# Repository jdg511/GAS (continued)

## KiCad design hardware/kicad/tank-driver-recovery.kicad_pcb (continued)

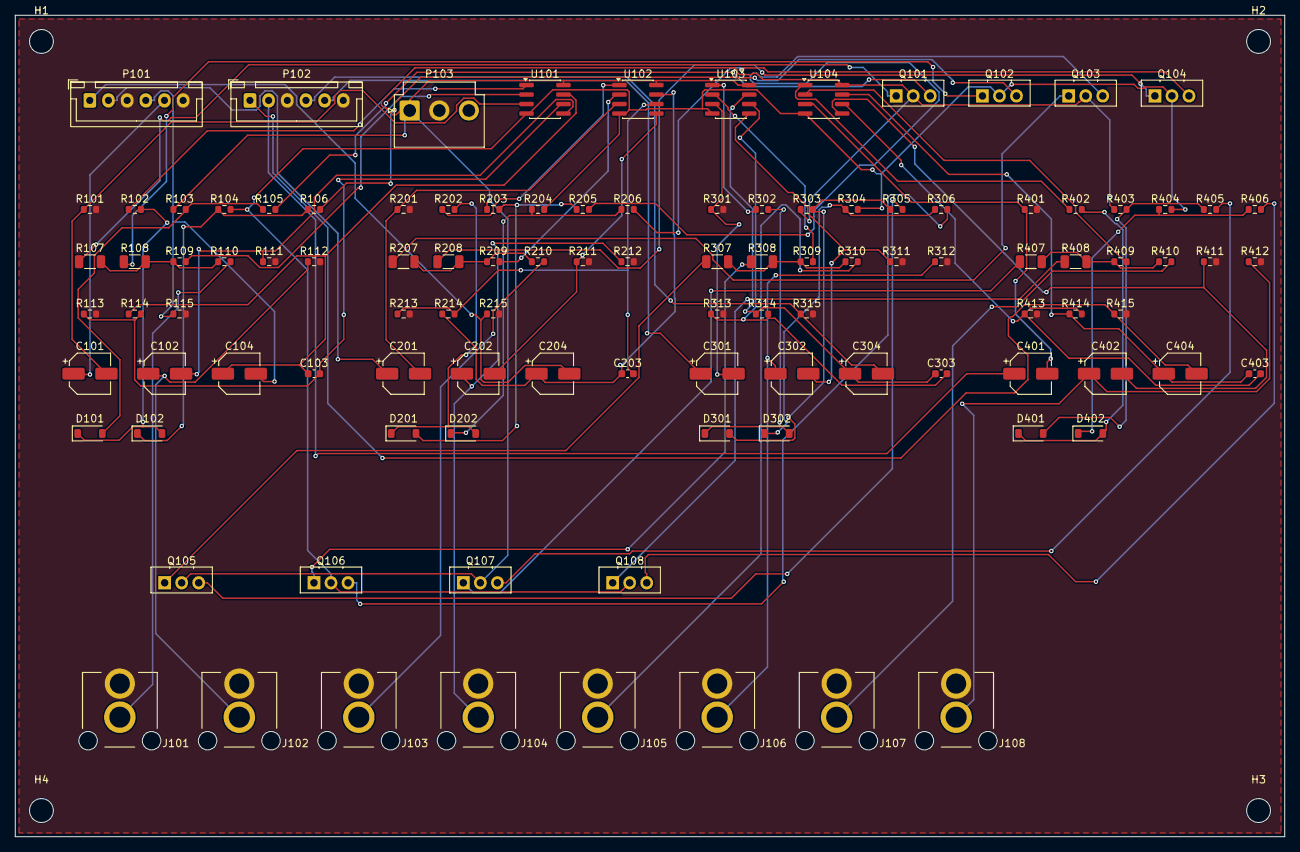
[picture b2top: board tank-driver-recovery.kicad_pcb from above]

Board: 2 copper layers, 170.0 x 110.0 mm, 111 parts (0 on the bottom side), 75 nets.

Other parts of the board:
H1, H2, H3, H4: M3 NPTH; MountingHole_3.2mm_M3
